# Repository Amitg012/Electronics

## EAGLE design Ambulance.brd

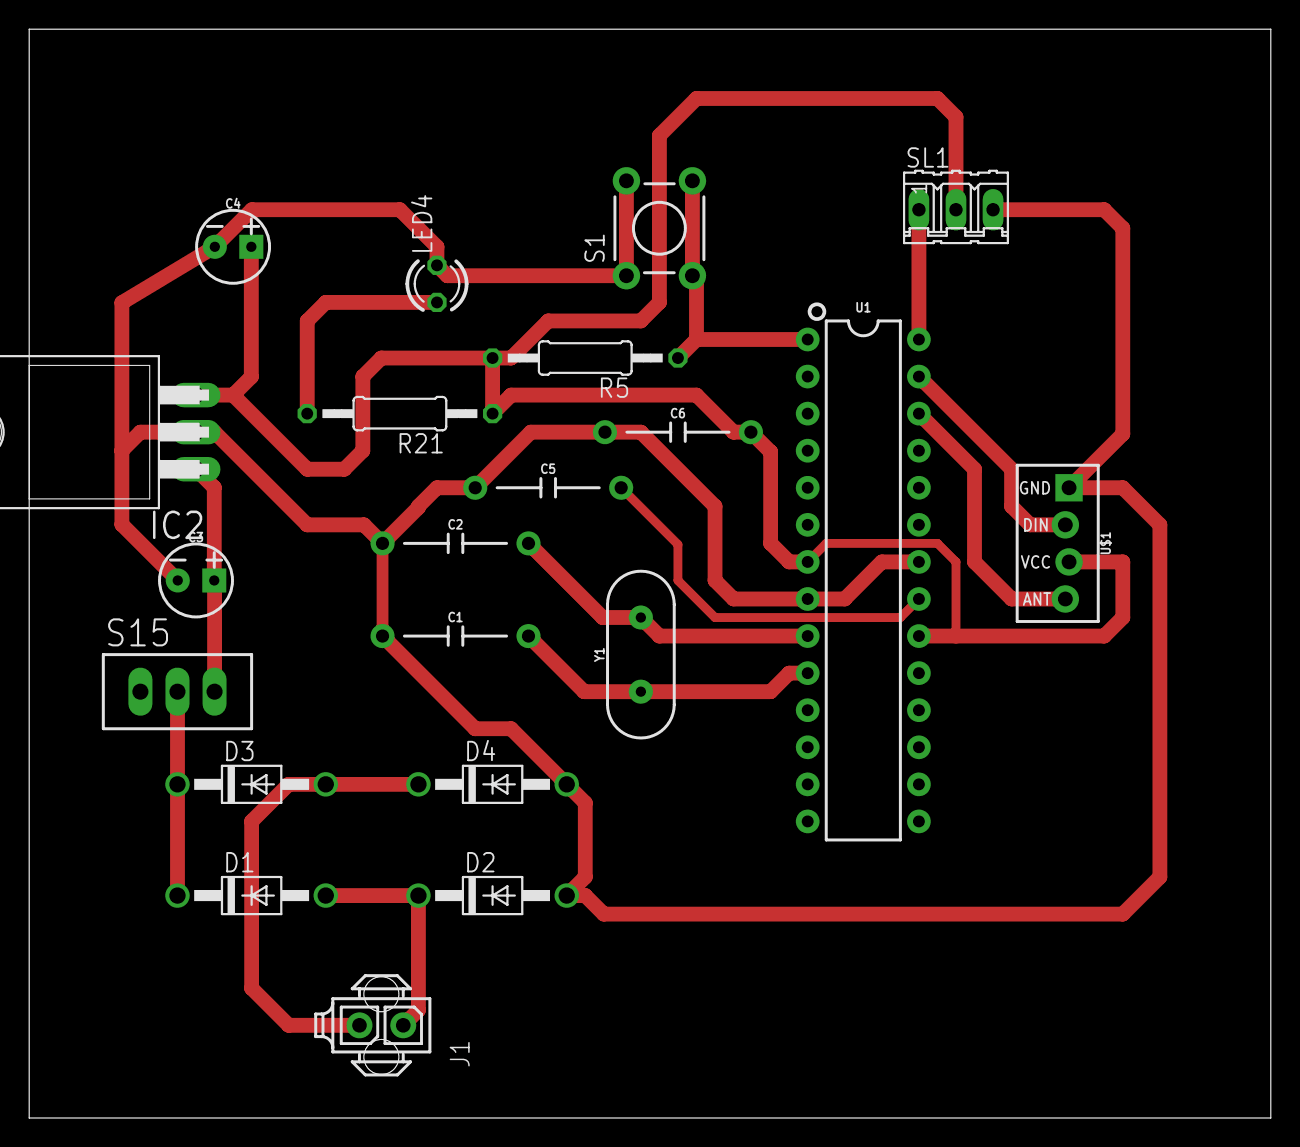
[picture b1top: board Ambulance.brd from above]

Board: 2 copper layers, 85.1 x 74.6 mm, 21 parts (0 on the bottom side), 14 nets.

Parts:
C1, C2, C5, C6: 10nF; CAP-PTH-10MM
C3, C4: 10uF; CPOL-RADIAL-2.5MM-5MM-KIT
D1, D2, D3, D4: 1N4004; DO41-10
IC2: 7812T; TO220H
J1: 794681-2
LED4: TLLR4400; LED3MM
R5, R21: 0207/12
S1: TACTILE-PTH
S15: TL37PO; TL3XPO
SL1: 03P
U1: 328P; DIP28
U$1: RF-LINK_TX
Y1: 16MHz; HC49US

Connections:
5V: C4.1, C6.2, IC2.3, R5.2, R21.1, SL1.2, U1.7, U1.20, U$1.VCC
12V: D1.C, D3.C, S15.2
GND: C1.1, C2.1, C3.2, C4.2, C5.1, C6.1, D2.A, D4.A, IC2.2, LED4.K, S1.1, S1.2, SL1.3, U1.8, U1.22, U$1.GND
unnamed: SL1.1, U1.28
unnamed: U1.27, U$1.DATA
unnamed: C2.2, U1.9, Y1.2
unnamed: C1.2, U1.10, Y1.1
unnamed: LED4.A, R21.2
unnamed: C5.2, U1.21
unnamed: U1.26, U$1.ANT
unnamed: R5.1, S1.3, S1.4, U1.1
unnamed: D3.A, D4.C, J1.2
unnamed: C3.1, IC2.1, S15.3
unnamed: D1.A, D2.C, J1.1

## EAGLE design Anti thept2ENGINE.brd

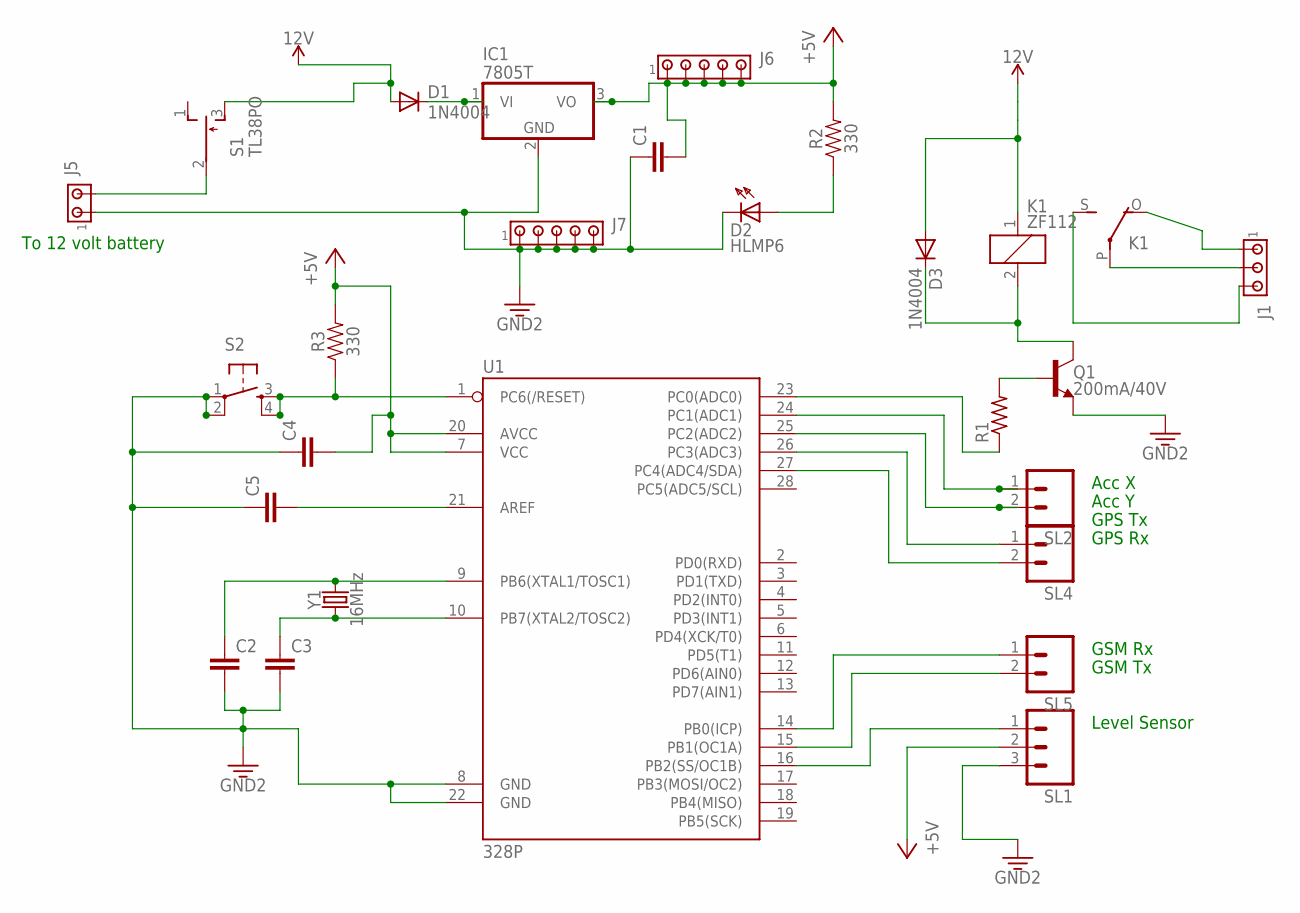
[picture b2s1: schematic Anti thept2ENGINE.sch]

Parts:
C1, C2, C3, C4, C5: C5/2.5; C5B2.5
D1, D3: 1N4004; DO41-10
D2: HLMP6
IC1: 7805T; TO220H
J1: MTA03-156; 1X3MTA
J5: MTA02-156; 1X2MTA
J6, J7: MTA05-100; 10X05MTA
K1: ZF112
Q1: 200mA/40V; TO-92
R1: R-US_0204/7; 0204/7
R2, R3: 330; AXIAL-0.3
S1: TL38PO; TL3XPO
S2: TAC_SWITCHPTH; TACTILE-PTH
SL1: M03; 03P
SL2, SL4, SL5: M02; 02P
U1: 328P; DIP28
Y1: 16MHz; HC49US

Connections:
3.3V: C1.1, C2.2, C3.2, C4.1, C5.1, D2.K, IC1.2 (GND), J5.1, J7.2, J7.3, J7.4, J7.5, Q1.1 (E), SL1.3, U1.8 (GND), U1.22 (GND)
12V: D1.A, D3.A, K1.1, S1.3 (S)
+5V: C1.2, C4.2, IC1.3 (VO), J6.1, J6.2, J6.3, J6.4, J6.5, R2.P$2 (2), R3.P$2 (2), SL1.2, U1.7 (VCC), U1.20 (AVCC)
unnamed: J1.1, K1.O
unnamed: J1.2, K1.P
unnamed: Q1.2 (B), R1.2
unnamed: D3.C, K1.2, Q1.3 (C)
unnamed: J1.3, K1.S
unnamed: R1.1, U1.23 (PC0(ADC0))
unnamed: D2.A, R2.P$1 (1)
unnamed: C3.1, U1.10 (PB7(XTAL2/TOSC2)), Y1.1
unnamed: SL2.1, U1.24 (PC1(ADC1))
unnamed: R3.P$1 (1), S2.3, S2.4, U1.1 (PC6(/RESET))
unnamed: SL2.2, U1.25 (PC2(ADC2))
unnamed: C5.2, U1.21 (AREF)
unnamed: SL4.1, U1.26 (PC3(ADC3))
unnamed: J5.2, S1.2
unnamed 17: U1.2 (PD0(RXD)); also elsewhere on the board
unnamed: D1.C, IC1.1 (VI)
unnamed 19: U1.3 (PD1(TXD)); also elsewhere on the board
unnamed: C2.1, U1.9 (PB6(XTAL1/TOSC1)), Y1.2
unnamed: SL4.2, U1.27 (PC4(ADC4/SDA))
unnamed: SL5.1, U1.14 (PB0(ICP))
unnamed: S2.1, S2.2
unnamed: SL5.2, U1.15 (PB1(OC1A))
unnamed: SL1.1, U1.16 (PB2(SS/OC1B))

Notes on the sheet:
GPS Tx
GPS Rx
Acc X
Acc Y
GSM Tx
GSM Rx
To 12 volt battery
Level Sensor

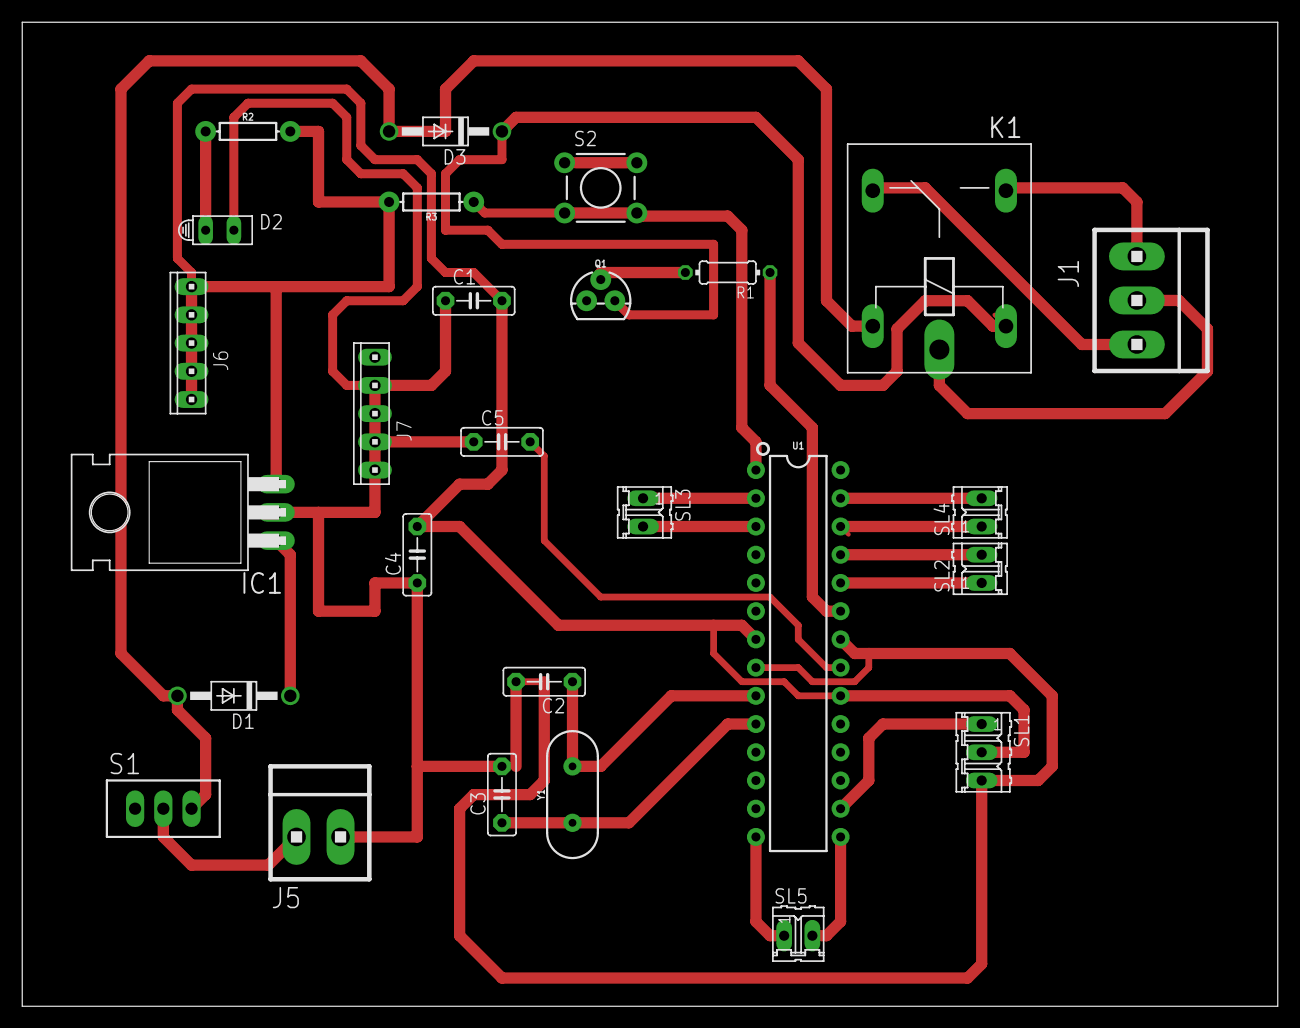
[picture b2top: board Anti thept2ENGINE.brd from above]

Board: 2 copper layers, 113.0 x 88.6 mm, 27 parts (0 on the bottom side), 26 nets.

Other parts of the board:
SL3: 02P

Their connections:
unnamed 17: SL3.1; also elsewhere on the board
unnamed 19: SL3.2; also elsewhere on the board

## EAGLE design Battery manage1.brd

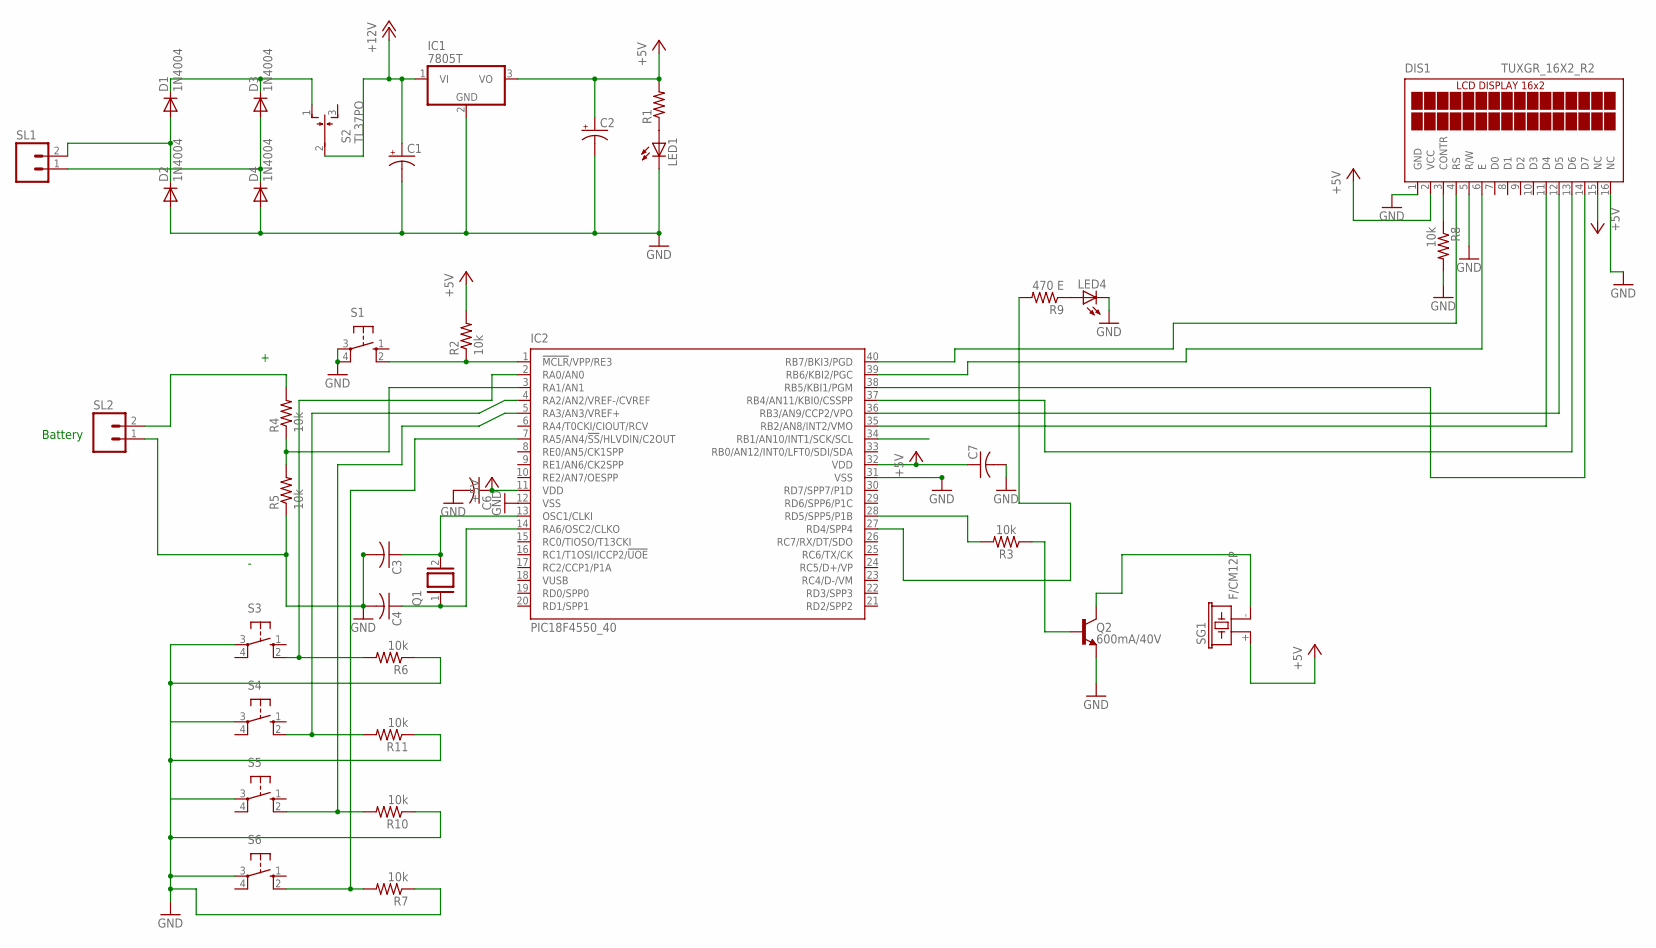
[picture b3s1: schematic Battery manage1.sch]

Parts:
C1, C2: CPOL-USE3.5-8; E3,5-8
C3, C4, C6, C7: C-US025-024X044; C025-024X044
D1, D2, D3, D4: 1N4004; DO41-10
DIS1: TUXGR_16X2_R2
IC1: 7805T; TO220H
IC2: PIC18F4550_40; DIL40
LED1, LED4: LED5MM
Q1: XTAL/S; QS
Q2: 600mA/40V; TO-92
R1: R-US_0207/10; 0207/10
R2, R4, R5, R6, R7, R8, R10, R11: 10k; 0207/10
R3: 10k; AXIAL-0.3
R9: 470 E; 0207/10
S1, S3, S4, S5, S6: 10-XX; B3F-10XX
S2: TL37PO; TL3XPO
SG1: F/CM12P
SL1, SL2: MA02; 02PA

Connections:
+5V: C2.+, C6.1, C7.1, DIS1.2 (VCC), DIS1.15 (NC), IC1.3 (VO), IC2.11 (VDD), IC2.32 (VDD), R1.2, R2.2, SG1.+ (1)
+12V: C1.+, IC1.1 (VI), S2.2
GND: C1.-, C2.-, C3.2, C4.2, C6.2, C7.2, D2.A, D4.A, DIS1.1 (GND), DIS1.5 (R/W), DIS1.16 (NC), IC1.2 (GND), IC2.12 (VSS), IC2.31 (VSS), LED1.K (C), LED4.K (C), Q2.3 (E), R5.1, R6.1, R7.1, R8.2, R10.1, R11.1, S1.3, S1.4 (P1), S3.3, S4.3, S5.3, S6.3, SL2.1
unnamed: D1.A, D2.C, SL1.2
unnamed: D3.A, D4.C, SL1.1
unnamed: IC2.2 (RA0/AN0), R6.2, S3.2 (S1)
unnamed: LED1.A, R1.1
unnamed: IC2.4 (RA2/AN2/VREF-/CVREF), R11.2, S4.2 (S1)
unnamed: DIS1.11 (D4), IC2.35 (RB2/AN8/INT2/VMO)
unnamed: R4.2, SL2.2
unnamed: IC2.28 (RD5/SPP5/P1B), R3.P$2 (2)
unnamed: IC2.1 (!MCLR!/VPP/RE3), R2.1, S1.2 (S1)
unnamed: Q2.2 (B), R3.P$1 (1)
unnamed: DIS1.4 (RS), IC2.40 (RB7/BKI3/PGD)
unnamed: DIS1.6 (E), IC2.39 (RB6/KBI2/PGC)
unnamed: Q2.1 (C), SG1.- (2)
unnamed: IC2.27 (RD4/SPP4), R9.2
unnamed: LED4.A, R9.1
unnamed: IC2.3 (RA1/AN1), R4.1, R5.2
unnamed: IC2.5 (RA3/AN3/VREF+), R10.2, S5.2 (S1)
unnamed: IC2.7 (RA5/AN4/!SS!/HLVDIN/C2OUT), R7.2, S6.2 (S1)
unnamed: C4.1, IC2.14 (RA6/OSC2/CLKO), Q1.1
unnamed: C3.1, IC2.13 (OSC1/CLKI), Q1.2
unnamed: DIS1.14 (D7), IC2.38 (RB5/KBI1/PGM)
unnamed: DIS1.13 (D6), IC2.37 (RB4/AN11/KBI0/CSSPP)
unnamed: DIS1.12 (D5), IC2.36 (RB3/AN9/CCP2/VPO)
unnamed: DIS1.3 (CONTR), R8.1
unnamed: D1.C, D3.C, S2.1 (O)

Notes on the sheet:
Battery

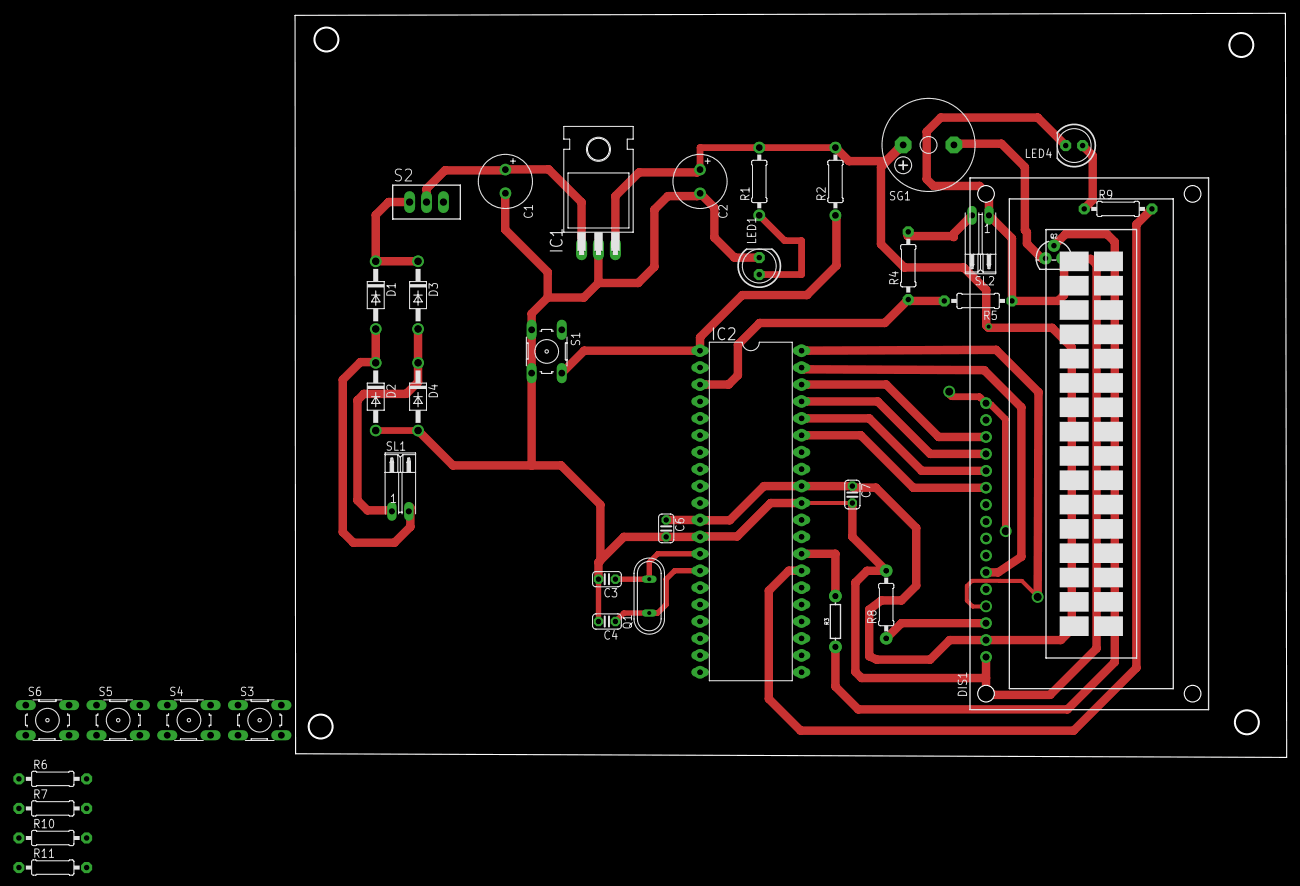
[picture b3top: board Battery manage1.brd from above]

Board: 2 copper layers, 148.8 x 111.7 mm, 37 parts (0 on the bottom side), 28 nets.

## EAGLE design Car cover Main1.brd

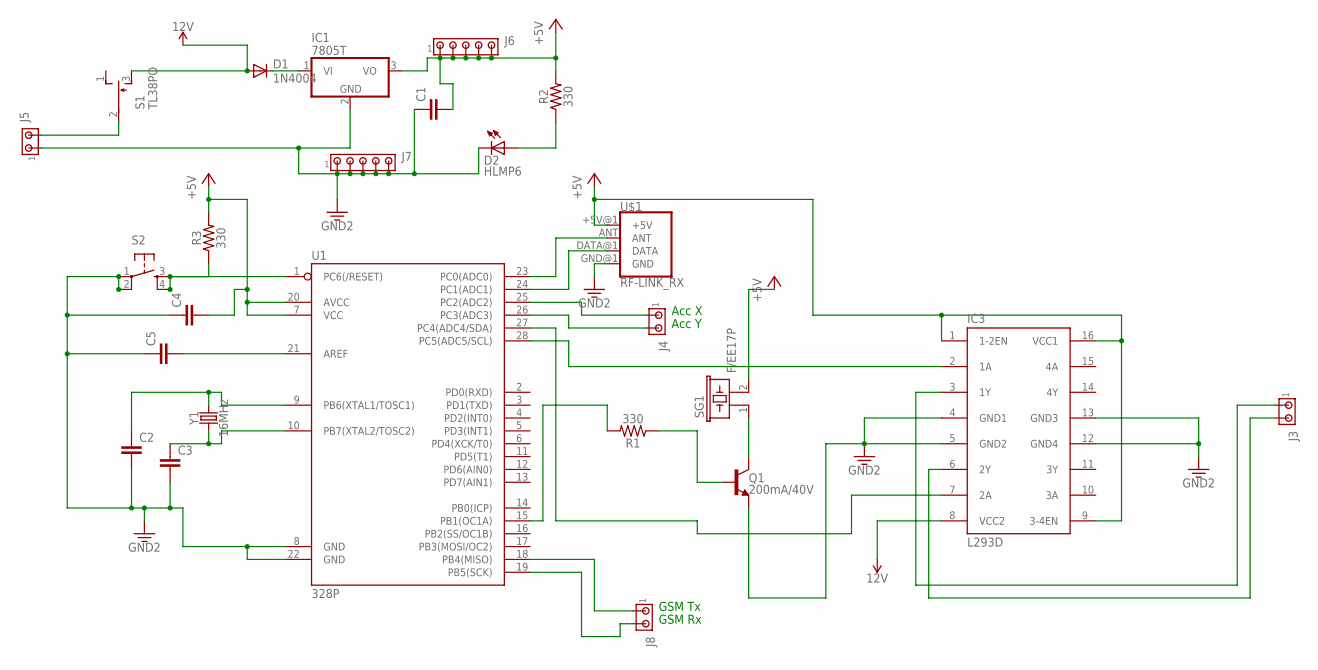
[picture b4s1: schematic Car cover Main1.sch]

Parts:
C1, C2, C3, C4, C5: C5/2.5; C5B2.5
D1: 1N4004; DO41-10
D2: HLMP6
IC1: 7805T; TO220H
IC3: L293D; DIL16
J3, J4, J5, J8: MTA02-156; 1X2MTA
J6, J7: MTA05-100; 10X05MTA
Q1: 200mA/40V; TO-92
R1, R2, R3: 330; AXIAL-0.3
S1: TL38PO; TL3XPO
S2: TAC_SWITCHPTH; TACTILE-PTH
SG1: F/EE17P
U1: 328P; DIP28
U$1: RF-LINK_RX
Y1: 16MHz; HC49US

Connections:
3.3V: C1.1, C2.2, C3.2, C4.1, C5.1, D2.K, IC1.2 (GND), IC3.4 (GND1), IC3.5 (GND2), IC3.12 (GND4), IC3.13 (GND3), J5.1, J7.1, J7.2, J7.3, J7.4, J7.5, Q1.1 (E), S2.1, S2.2, U1.8 (GND), U1.22 (GND), U$1.GND@1 (GND)
12V: D1.A, IC3.8 (VCC2), S1.3 (S)
+5V: C1.2, C4.2, IC1.3 (VO), IC3.1 (1-2EN), IC3.9 (3-4EN), IC3.16 (VCC1), J6.1, J6.2, J6.3, J6.4, J6.5, R2.P$2 (2), R3.P$2 (2), SG1.2, U1.7 (VCC), U1.20 (AVCC), U$1.+5V@1 (+5V)
unnamed: U1.23 (PC0(ADC0)), U$1.ANT
unnamed: J4.1, U1.25 (PC2(ADC2))
unnamed: J4.2, U1.26 (PC3(ADC3))
unnamed: J8.1, U1.18 (PB4(MISO))
unnamed: J8.2, U1.19 (PB5(SCK))
unnamed: IC3.2 (1A), U1.28 (PC5(ADC5/SCL))
unnamed: D2.A, R2.P$1 (1)
unnamed: Q1.2 (B), R1.P$1 (1)
unnamed: IC3.7 (2A), U1.27 (PC4(ADC4/SDA))
unnamed: R3.P$1 (1), S2.3, S2.4, U1.1 (PC6(/RESET))
unnamed: C3.1, U1.10 (PB7(XTAL2/TOSC2)), Y1.1
unnamed: C5.2, U1.21 (AREF)
unnamed: IC3.3 (1Y), J3.1
unnamed: J5.2, S1.2
unnamed: IC3.6 (2Y), J3.2
unnamed: D1.C, IC1.1 (VI)
unnamed: R1.P$2 (2), U1.15 (PB1(OC1A))
unnamed: U1.24 (PC1(ADC1)), U$1.DATA@1 (DATA)
unnamed: Q1.3 (C), SG1.1
unnamed: C2.1, U1.9 (PB6(XTAL1/TOSC1)), Y1.2

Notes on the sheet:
Acc X
Acc Y
GSM Tx
GSM Rx

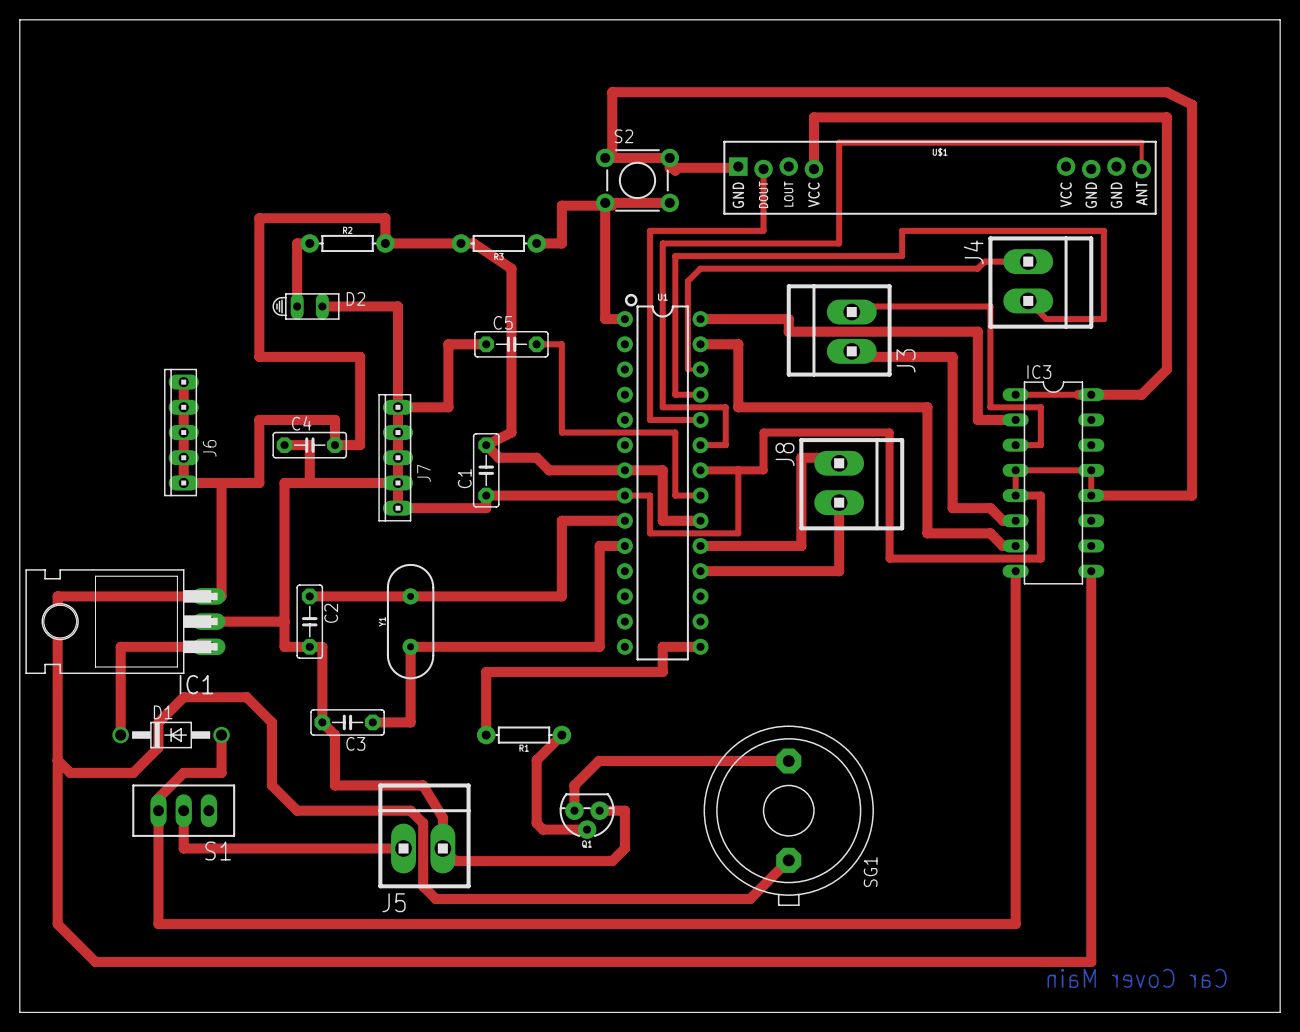
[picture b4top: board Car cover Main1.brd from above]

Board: 2 copper layers, 127.0 x 100.0 mm, 25 parts (0 on the bottom side), 23 nets.

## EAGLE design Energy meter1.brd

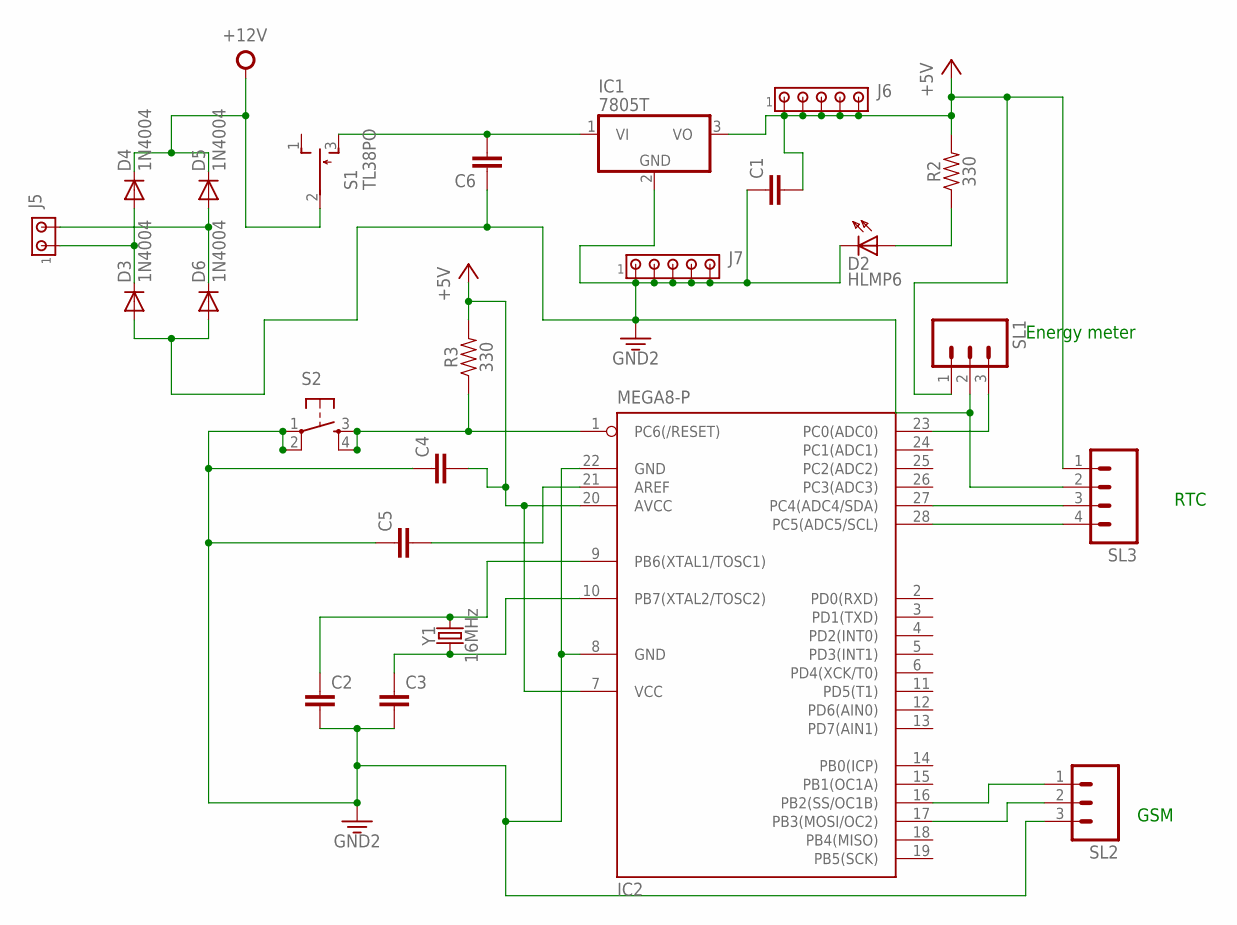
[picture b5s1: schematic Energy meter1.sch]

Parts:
C1, C2, C3, C4, C5, C6: C5/2.5; C5B2.5
D2: HLMP6
D3, D4, D5, D6: 1N4004; DO41-10
IC1: 7805T; TO220H
IC2: MEGA8-P; DIL28-3
J5: MTA02-156; 1X2MTA
J6, J7: MTA05-100; 10X05MTA
R2, R3: 330; AXIAL-0.3
S1: TL38PO; TL3XPO
S2: TAC_SWITCHPTH; TACTILE-PTH
SL1, SL2: MA03; 03P
SL3: MA04; 04PA
Y1: 16MHz; HC49US

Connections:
3.3V: C1.1, C2.2, C3.2, C4.1, C5.1, C6.1, D2.K, D3.A, D6.A, IC1.2 (GND), IC2.8 (GND), IC2.22 (GND), J7.1, J7.2, J7.3, J7.4, J7.5, S2.1, S2.2, SL1.2, SL2.3, SL3.2
+5V: C1.2, C4.2, IC1.3 (VO), IC2.7 (VCC), IC2.20 (AVCC), J6.1, J6.2, J6.3, J6.4, J6.5, R2.P$2 (2), R3.P$2 (2), SL1.1, SL3.1
+12V: D4.C, D5.C, S1.2
unnamed: IC2.1 (PC6(/RESET)), R3.P$1 (1), S2.3, S2.4
unnamed: IC2.23 (PC0(ADC0)), SL1.3
unnamed: D3.C, D4.A, J5.1
unnamed: C5.2, IC2.21 (AREF)
unnamed: C2.1, IC2.9 (PB6(XTAL1/TOSC1)), Y1.2
unnamed: IC2.16 (PB2(SS/OC1B)), SL2.1
unnamed: D2.A, R2.P$1 (1)
unnamed: C3.1, IC2.10 (PB7(XTAL2/TOSC2)), Y1.1
unnamed: D5.A, D6.C, J5.2
unnamed: IC2.17 (PB3(MOSI/OC2)), SL2.2
unnamed: IC2.27 (PC4(ADC4/SDA)), SL3.3
unnamed: IC2.28 (PC5(ADC5/SCL)), SL3.4
unnamed: C6.2, IC1.1 (VI), S1.3 (S)

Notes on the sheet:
Energy meter
GSM
RTC

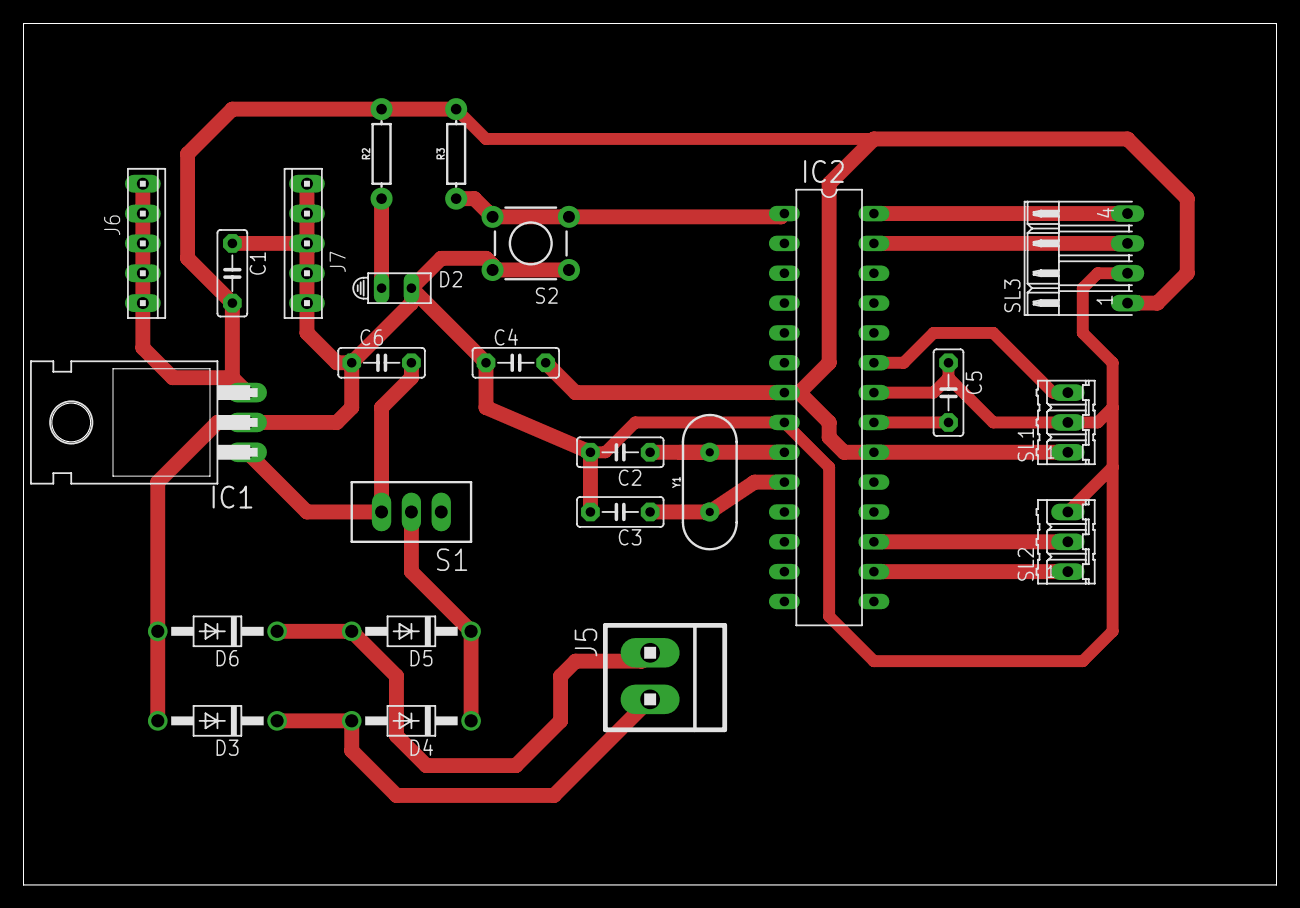
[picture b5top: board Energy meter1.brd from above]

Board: 2 copper layers, 106.7 x 73.3 mm, 24 parts (0 on the bottom side), 16 nets.

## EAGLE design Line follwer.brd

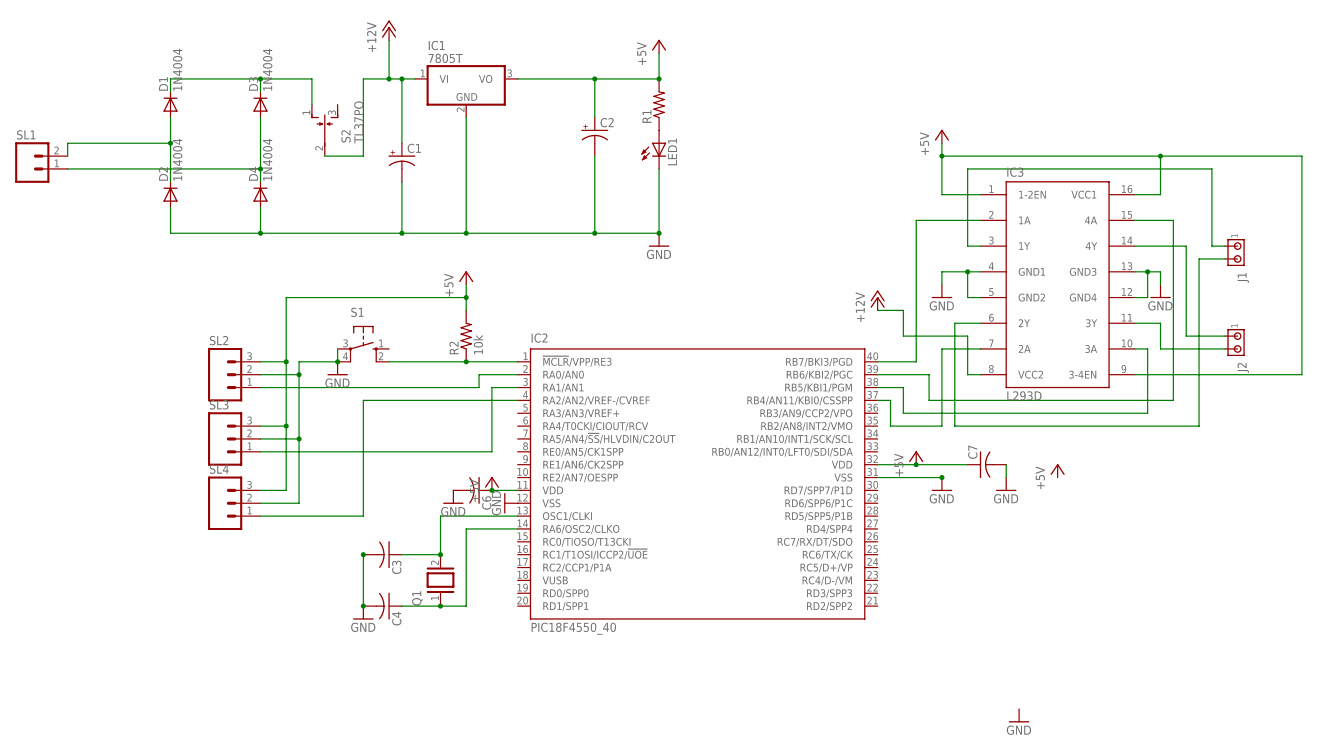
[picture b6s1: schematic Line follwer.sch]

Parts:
C1, C2: CPOL-USE3.5-8; E3,5-8
C3, C4, C6, C7: C-US025-024X044; C025-024X044
D1, D2, D3, D4: 1N4004; DO41-10
IC1: 7805T; TO220H
IC2: PIC18F4550_40; DIL40
IC3: L293D; DIL16
J1, J2: MTA02-100; 10X02MTA
LED1: LED5MM
Q1: XTAL/S; QS
R1: R-US_0207/10; 0207/10
R2: 10k; 0207/10
S1: 10-XX; B3F-10XX
S2: TL37PO; TL3XPO
SL1: MA02; 02PA
SL2, SL3, SL4: MA03; 03P

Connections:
+5V: C2.+, C6.1, C7.1, IC1.3 (VO), IC2.11 (VDD), IC2.32 (VDD), IC3.1 (1-2EN), IC3.9 (3-4EN), IC3.16 (VCC1), R1.2, R2.2, SL2.3, SL3.3, SL4.3
+12V: C1.+, IC1.1 (VI), IC3.8 (VCC2), S2.2
GND: C1.-, C2.-, C3.2, C4.2, C6.2, C7.2, D2.A, D4.A, IC1.2 (GND), IC2.12 (VSS), IC2.31 (VSS), IC3.4 (GND1), IC3.5 (GND2), IC3.12 (GND4), IC3.13 (GND3), LED1.K (C), S1.3, S1.4 (P1), SL2.2, SL3.2, SL4.2
unnamed: IC2.40 (RB7/BKI3/PGD), IC3.2 (1A)
unnamed: D1.A, D2.C, SL1.2
unnamed: D3.A, D4.C, SL1.1
unnamed: IC2.37 (RB4/AN11/KBI0/CSSPP), IC3.7 (2A)
unnamed: IC2.39 (RB6/KBI2/PGC), IC3.15 (4A)
unnamed: LED1.A, R1.1
unnamed: IC2.38 (RB5/KBI1/PGM), IC3.10 (3A)
unnamed: IC3.3 (1Y), J1.1
unnamed: IC3.6 (2Y), J1.2
unnamed: IC3.14 (4Y), J2.1
unnamed: IC2.1 (!MCLR!/VPP/RE3), R2.1, S1.2 (S1)
unnamed: IC3.11 (3Y), J2.2
unnamed: IC2.2 (RA0/AN0), SL2.1
unnamed: IC2.3 (RA1/AN1), SL3.1
unnamed: IC2.4 (RA2/AN2/VREF-/CVREF), SL4.1
unnamed: C4.1, IC2.14 (RA6/OSC2/CLKO), Q1.1
unnamed: C3.1, IC2.13 (OSC1/CLKI), Q1.2
unnamed: D1.C, D3.C, S2.1 (O)

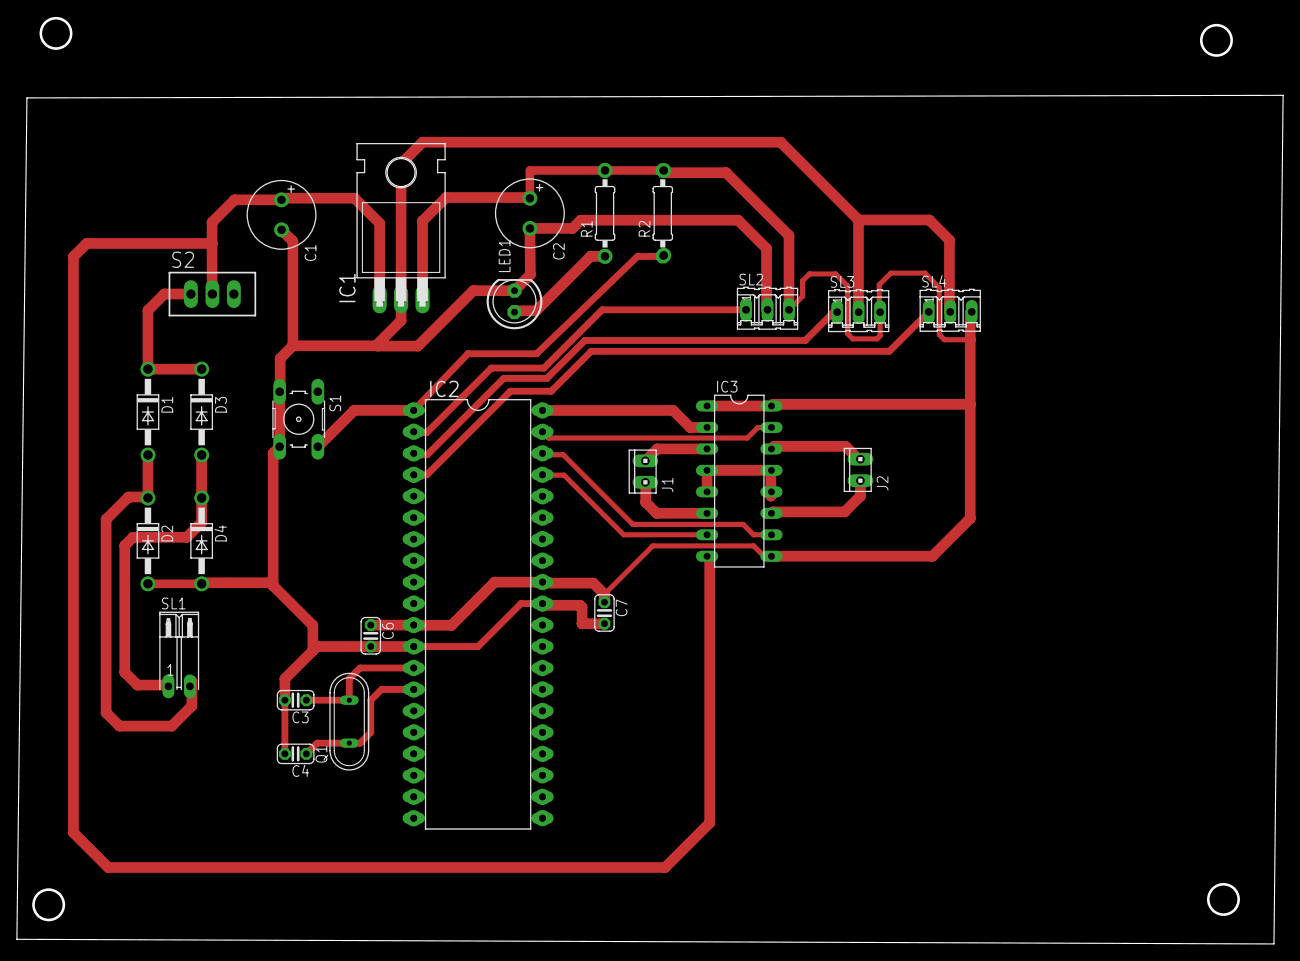
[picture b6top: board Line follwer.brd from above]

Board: 2 copper layers, 149.8 x 109.5 mm, 25 parts (0 on the bottom side), 21 nets.

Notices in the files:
parts and their libraries:
SparkFun-Capacitors: Licensing: Creative Commons ShareAlike 4.0 International - https://creativecommons.org/licenses/by-sa/4.0
